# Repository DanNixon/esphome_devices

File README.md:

# ESPHome devices 

Configuration, code and CAD for custom smarthome devices, powered by [ESPHome](https://esphome.io/).

## Boards

|Board|Module|SoC|Buy|Notes|
|-----|------|---|---|-----|
|[LILYGO T-Internet POE](https://www.lilygo.cc/products/t-internet-poe)|[ESP32-WROOM-32E](https://www.espressif.com/sites/default/files/documentation/esp32-wroom-32e_esp32-wroom-32ue_datasheet_en.pdf)|[ESP32-D0WD-V3](https://www.espressif.com/sites/default/files/documentation/esp32_datasheet_en.pdf)|[AliExpress](https://www.aliexpress.com/item/4001122992446.html)||
|DOIT ESP32 DevKit USB-C|[ESP32-WROOM-32](https://www.espressif.com/sites/default/files/documentation/esp32-wroom-32_datasheet_en.pdf)|[ESP32-D0WDQ6](https://www.espressif.com/sites/default/files/documentation/esp32_datasheet_en.pdf)|[AliExpress](https://www.aliexpress.com/item/1005005495948290.html)||
|WeMos D1 Mini|TODO|[ESP8266](https://www.espressif.com/sites/default/files/documentation/esp8266-technical_reference_en.pdf)|TODO||

## Peripherals

|Type|Part|ESPHome|Buy|Notes|
|----|----|-------|---|-----|
|Temperature sensor|DS18B20|[`dallas`](https://esphome.io/components/sensor/dallas)|[AliExpress](https://www.aliexpress.com/item/1783091649.html)||
|VOC and NOx sensor|SGP41|[`sgp4x`](https://esphome.io/components/sensor/sgp4x)|[AliExpress](https://www.aliexpress.com/item/4000037083952.html)||
|CO2 sensor|SenseAir S8|[`senseair`](https://esphome.io/components/sensor/senseair)|[AliExpress](https://www.aliexpress.com/item/1005004123170360.html)|[datasheet](https://rmtplusstoragesenseair.blob.core.windows.net/docs/publicerat/PSP107.pdf)|
|Particulate matter sensor|PMS5003|[`pmsx003`](https://esphome.io/components/sensor/pmsx003)|[AliExpress](https://www.aliexpress.com/item/32944660534.html)||
|Temperature and humidity sensor|AHT20|[`aht10`](https://esphome.io/components/sensor/aht10)|[AliExpress](https://www.aliexpress.com/item/4000052449080.html)||
|Light sensor|BH1750|[`bh1750`](https://esphome.io/components/sensor/bh1750)|[AliExpress](https://www.aliexpress.com/item/1005001621873442.html)||
|IO expander|SX1509|[`sx1509`](https://esphome.io/components/sx1509)|[AliExpress](https://www.aliexpress.com/item/1005003891847975.html)||

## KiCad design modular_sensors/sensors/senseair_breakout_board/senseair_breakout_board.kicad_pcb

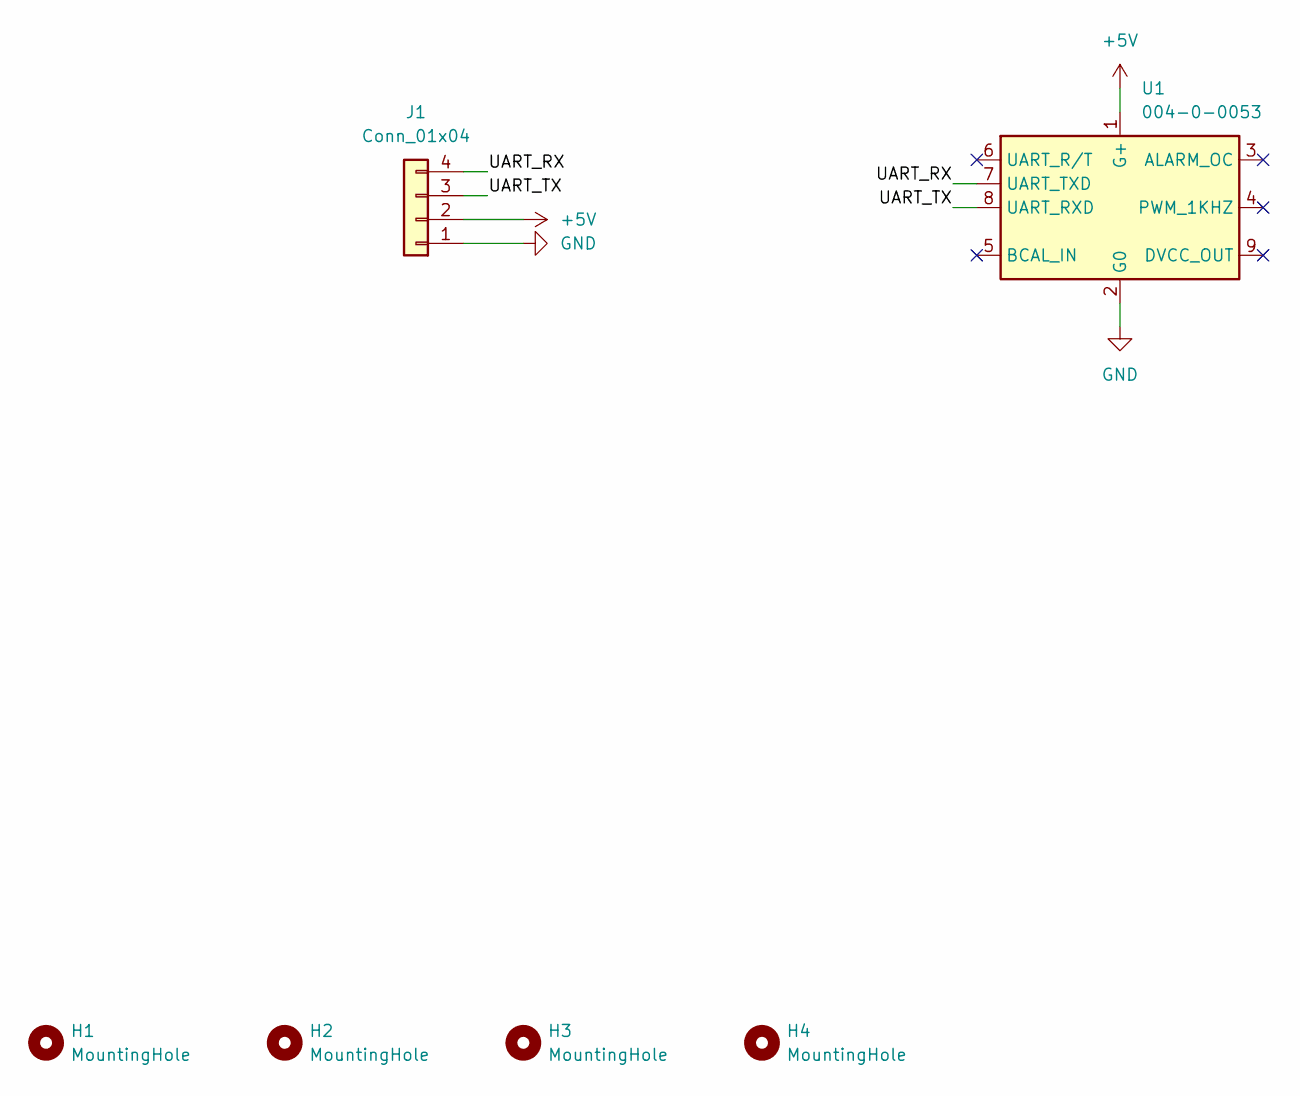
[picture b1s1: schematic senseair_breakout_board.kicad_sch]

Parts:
H1, H2, H3, H4: MountingHole; MountingHole_3.2mm_M3
J1: Conn_01x04; PinHeader_1x04_P2.54mm_Horizontal
U1: 004-0-0053; Senseair_S8_Down

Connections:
+5V: J1.2, U1.1 (G+)
/UART_RX: J1.4, U1.7 (UART_TXD)
/UART_TX: J1.3, U1.8 (UART_RXD)
GND: J1.1, U1.2 (G0)

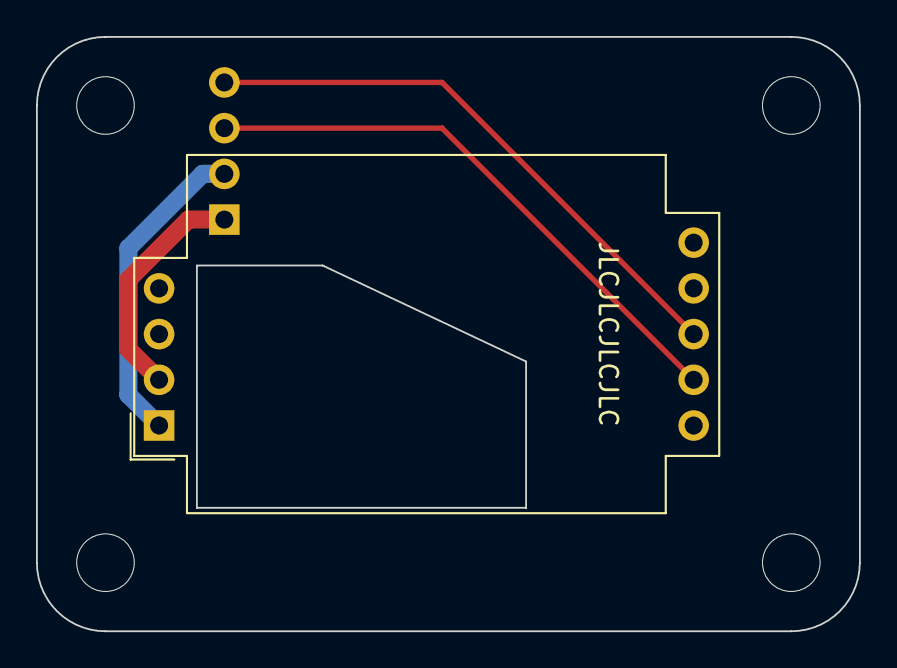
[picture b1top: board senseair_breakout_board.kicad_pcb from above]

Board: 2 copper layers, 45.7 x 33.0 mm, 6 parts (1 on the bottom side), 4 nets.

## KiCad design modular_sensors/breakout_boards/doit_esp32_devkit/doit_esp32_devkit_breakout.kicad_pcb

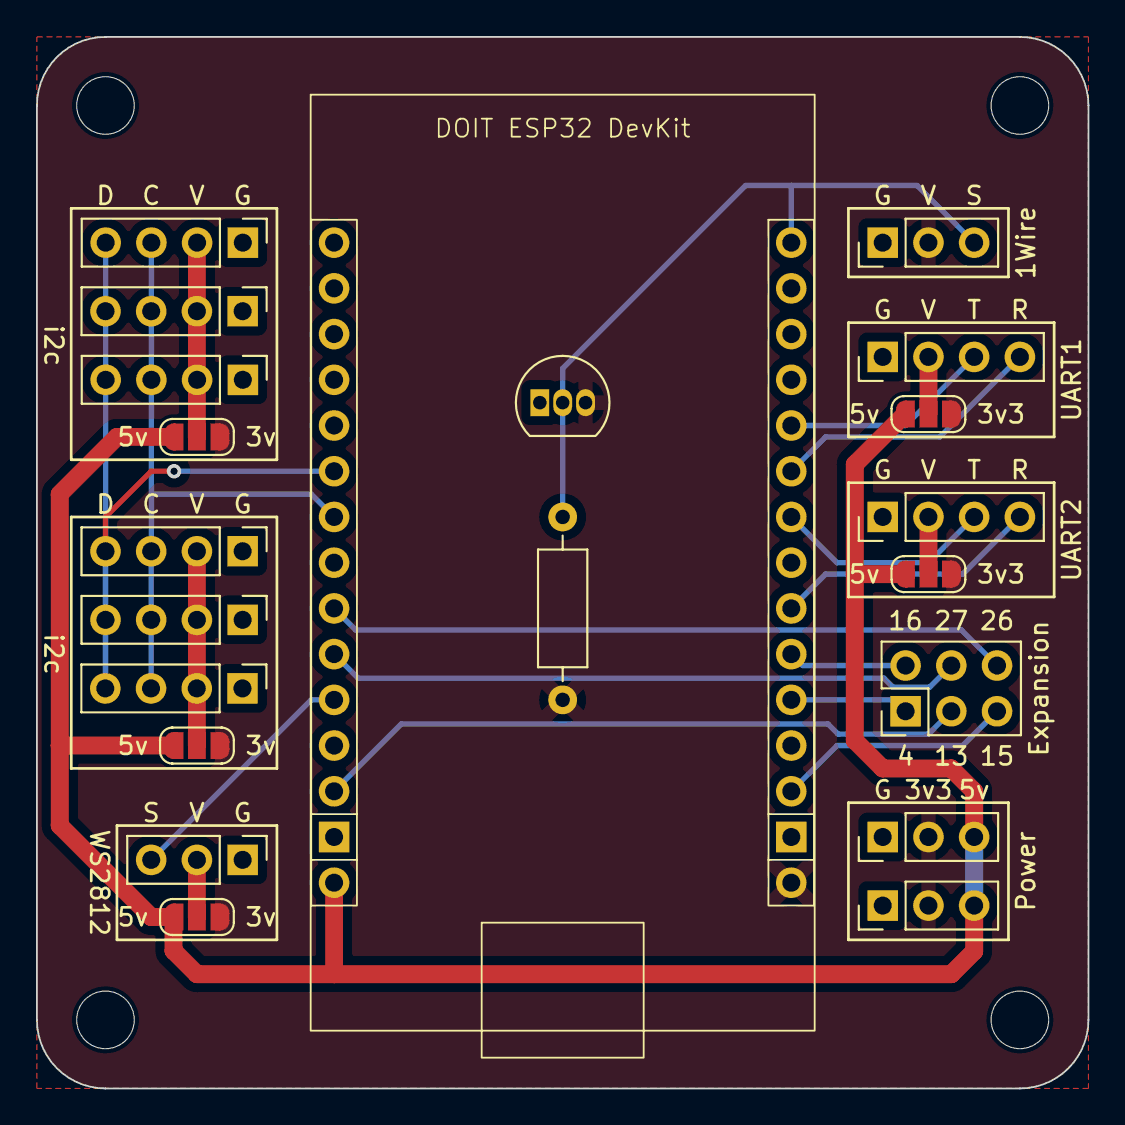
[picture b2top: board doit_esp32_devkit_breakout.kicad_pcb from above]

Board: 2 copper layers, 58.4 x 58.4 mm, 25 parts (0 on the bottom side), 22 nets.

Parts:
H1, H2, H3, H4: MountingHole; MountingHole_3.2mm_M3
J1: UART1; PinHeader_1x04_P2.54mm_Vertical
J2, J3: Power; PinHeader_1x03_P2.54mm_Vertical
J4: UART2; PinHeader_1x04_P2.54mm_Vertical
J5: Expansion; PinHeader_2x03_P2.54mm_Vertical
J6: WS2812; PinHeader_1x03_P2.54mm_Vertical
J7: OneWire; PinHeader_1x03_P2.54mm_Vertical
J8, J9, J10, J11, J12, J13: i2c; PinHeader_1x04_P2.54mm_Vertical
JP1: WS2812 V; SolderJumper-3_P1.3mm_Open_RoundedPad1.0x1.5mm_NumberLabels
JP2: UART1 V; SolderJumper-3_P1.3mm_Open_RoundedPad1.0x1.5mm_NumberLabels
JP3: UART2 V; SolderJumper-3_P1.3mm_Open_RoundedPad1.0x1.5mm_NumberLabels
JP5, JP6: i2c V; SolderJumper-3_P1.3mm_Open_RoundedPad1.0x1.5mm_NumberLabels
R1: 4K7; R_Axial_DIN0207_L6.3mm_D2.5mm_P10.16mm_Horizontal
U1: DOIT-ESP32-DEVKIT
U2: DS18B20; TO-92_Inline

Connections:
+3.3V: J2.2, J3.2, J7.2, JP1.3 (B), JP2.3 (B), JP3.3 (B), JP5.3 (B), JP6.3 (B), R1.1, U1.30 (3V3), U2.3 (V_{DD})
+5V: J2.3, J3.3, JP1.1 (A), JP2.1 (A), JP3.1 (A), JP5.1 (A), JP6.1 (A), U1.15 (VIN)
/D4: J5.1, U1.26 (D4)
/D13: J5.3, U1.13 (D13)
/D15: J5.5, U1.28 (D15)
/D16: J5.2, U1.25 (D16)
/D26: J5.6, U1.9 (D26)
/D27: J5.4, U1.10 (D27)
/I2C_SCL: J8.3, J9.3, J10.3, J11.3, J12.3, J13.3, U1.7 (D33)
/I2C_SDA: J8.4, J9.4, J10.4, J11.4, J12.4, J13.4, U1.6 (D32)
/ONEWIRE: J7.3, R1.2, U1.16 (D23), U2.2 (DQ)
/UART1_RX: J1.4, U1.21 (D19)
/UART1_TX: J1.3, U1.20 (D21)
/UART2_RX: J4.4, U1.24 (D17)
/UART2_TX: J4.3, U1.22 (D18)
/WS2812: J6.3, U1.11 (D14)
GND: J1.1, J2.1, J3.1, J4.1, J6.1, J7.1, J8.1, J9.1, J10.1, J11.1, J12.1, J13.1, U1.14 (GND), U1.29 (GND), U2.1 (GND)
unnamed: J1.2, JP2.2 (C)
unnamed: J4.2, JP3.2 (C)
unnamed: J6.2, JP1.2 (C)
unnamed: J8.2, J10.2, J12.2, JP5.2 (C)
unnamed: J9.2, J11.2, J13.2, JP6.2 (C)

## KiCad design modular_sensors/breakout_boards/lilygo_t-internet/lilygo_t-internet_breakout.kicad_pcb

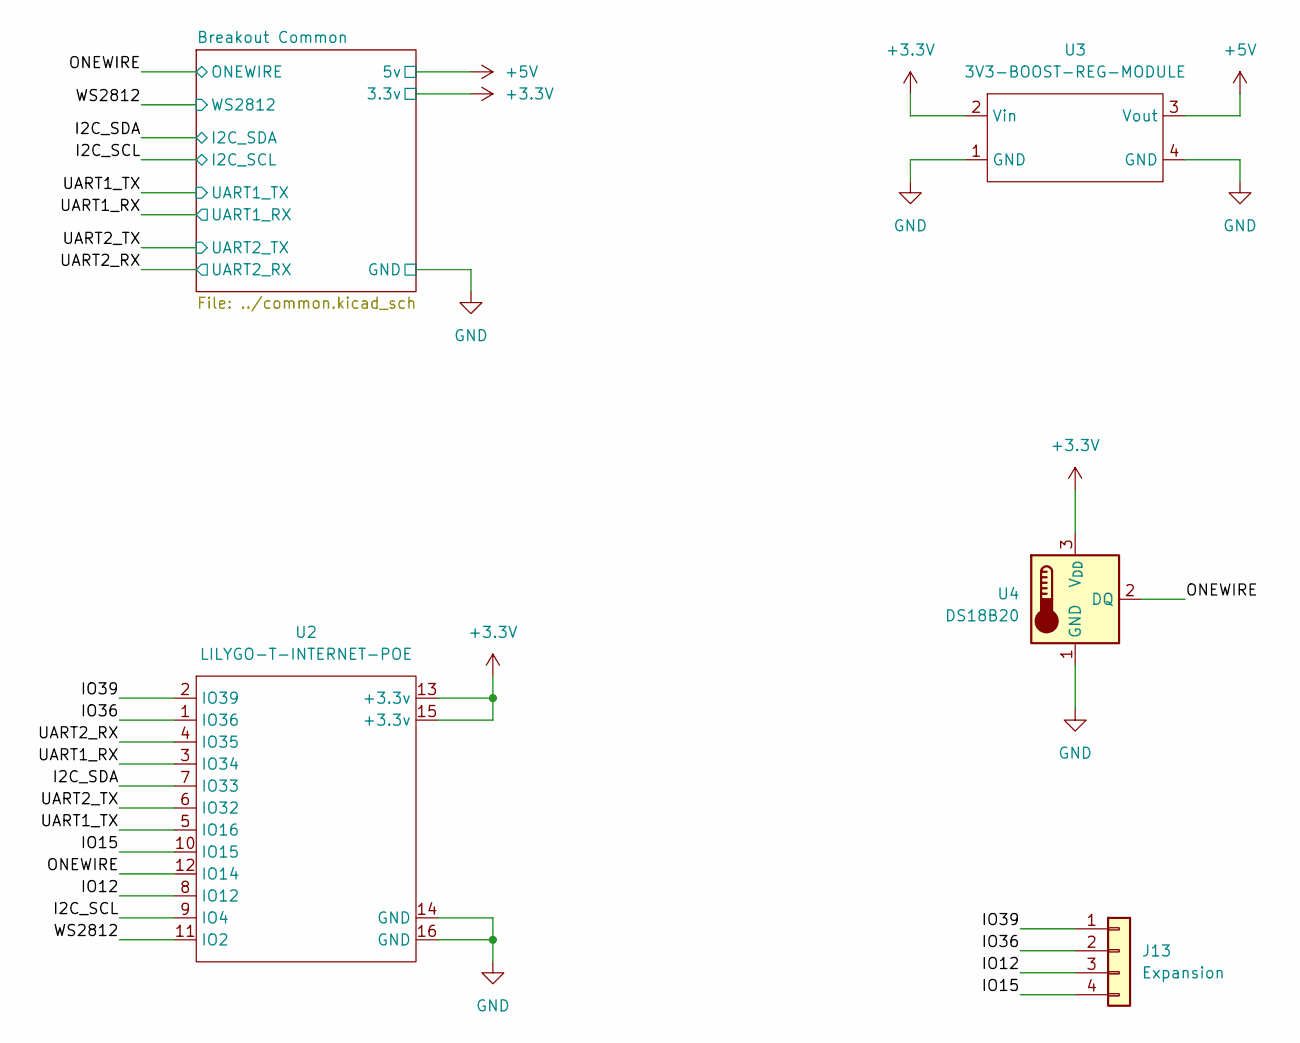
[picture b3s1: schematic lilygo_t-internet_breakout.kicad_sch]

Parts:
J13: Expansion; PinHeader_1x04_P2.54mm_Vertical
U2: LILYGO-T-INTERNET-POE
U3: 3V3-BOOST-REG-MODULE
U4: DS18B20; TO-92_Inline

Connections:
+3.3V: U2.13 (+3.3v), U2.15 (+3.3v), U3.2 (Vin), U4.3 (V_{DD}); also elsewhere on the board
+5V: U3.3 (Vout); also elsewhere on the board
/I2C_SCL: U2.9 (IO4); also elsewhere on the board
/I2C_SDA: U2.7 (IO33); also elsewhere on the board
/IO12: J13.3, U2.8 (IO12)
/IO15: J13.4, U2.10 (IO15)
/IO36: J13.2, U2.1 (IO36)
/IO39: J13.1, U2.2 (IO39)
/ONEWIRE: U2.12 (IO14), U4.2 (DQ); also elsewhere on the board
/UART1_RX: U2.3 (IO34); also elsewhere on the board
/UART1_TX: U2.5 (IO16); also elsewhere on the board
/UART2_RX: U2.4 (IO35); also elsewhere on the board
/UART2_TX: U2.6 (IO32); also elsewhere on the board
/WS2812: U2.11 (IO2); also elsewhere on the board
GND: U2.14 (GND), U2.16 (GND), U3.1 (GND), U3.4 (GND), U4.1 (GND); also elsewhere on the board

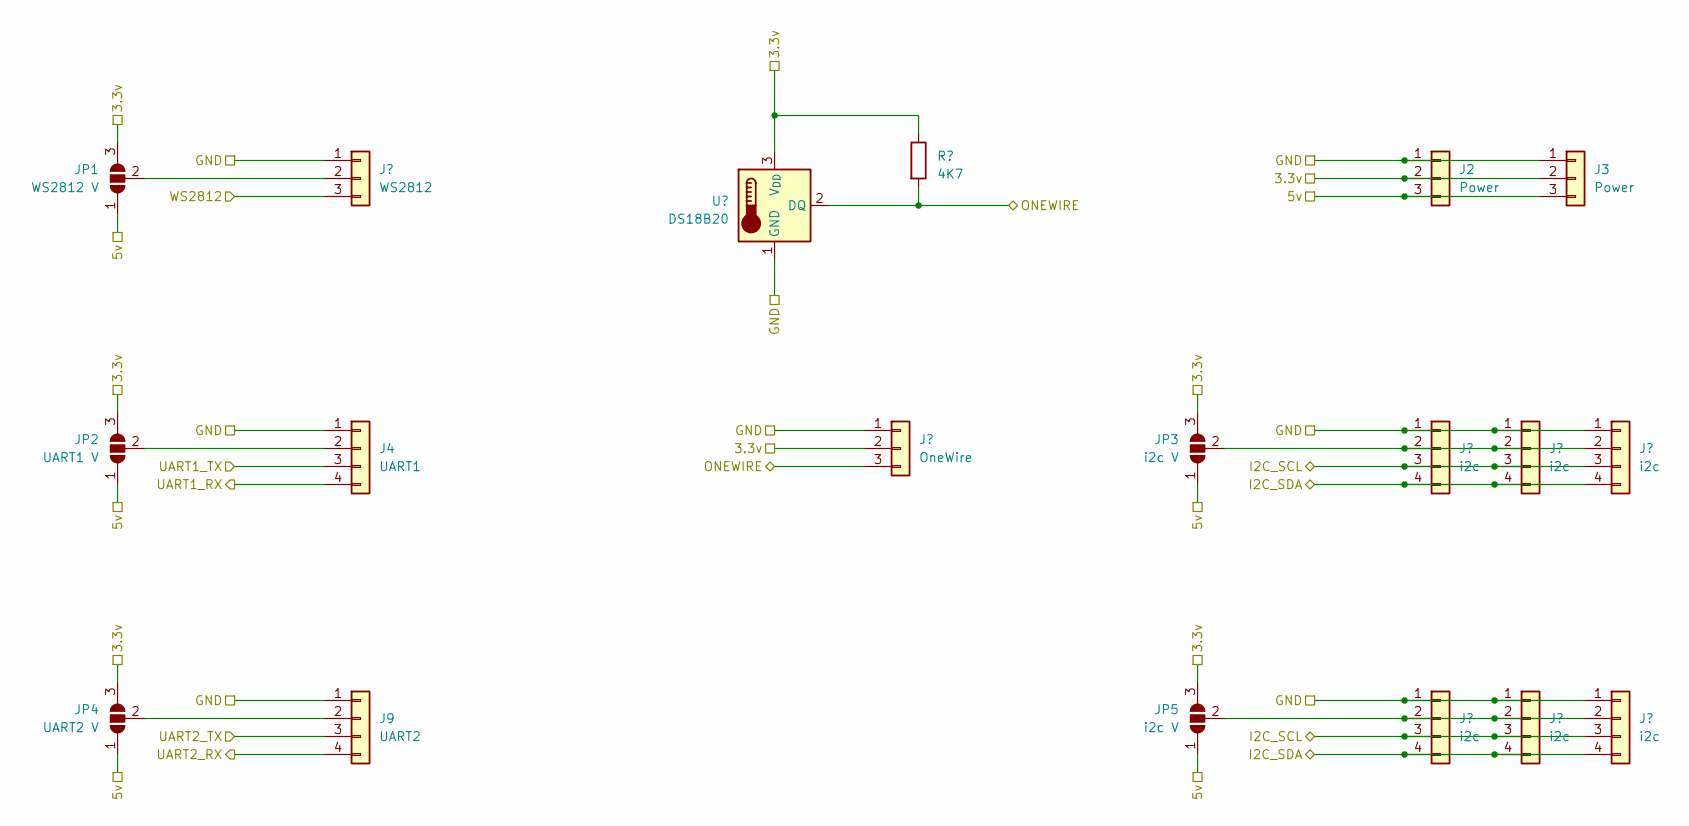
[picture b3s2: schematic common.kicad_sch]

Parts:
J1: WS2812; PinHeader_1x03_P2.54mm_Vertical
J2, J3: Power; PinHeader_1x03_P2.54mm_Vertical
J4: UART1; PinHeader_1x04_P2.54mm_Vertical
J5: OneWire; PinHeader_1x03_P2.54mm_Vertical
J6, J7, J8, J10, J11, J12: i2c; PinHeader_1x04_P2.54mm_Vertical
J9: UART2; PinHeader_1x04_P2.54mm_Vertical
JP1: WS2812 V; SolderJumper-3_P1.3mm_Open_RoundedPad1.0x1.5mm_NumberLabels
JP2: UART1 V; SolderJumper-3_P1.3mm_Open_RoundedPad1.0x1.5mm_NumberLabels
JP3, JP5: i2c V; SolderJumper-3_P1.3mm_Open_RoundedPad1.0x1.5mm_NumberLabels
JP4: UART2 V; SolderJumper-3_P1.3mm_Open_RoundedPad1.0x1.5mm_NumberLabels
R1: 4K7; R_Axial_DIN0207_L6.3mm_D2.5mm_P10.16mm_Horizontal
U1: DS18B20; TO-92_Inline

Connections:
+3.3V: J2.2, J3.2, J5.2, JP1.3 (B), JP2.3 (B), JP3.3 (B), JP4.3 (B), JP5.3 (B), R1.1, U1.3 (V_{DD}); also elsewhere on the board
+5V: J2.3, J3.3, JP1.1 (A), JP2.1 (A), JP3.1 (A), JP4.1 (A), JP5.1 (A); also elsewhere on the board
/I2C_SCL: J6.3, J7.3, J8.3, J10.3, J11.3, J12.3; also elsewhere on the board
/I2C_SDA: J6.4, J7.4, J8.4, J10.4, J11.4, J12.4; also elsewhere on the board
/ONEWIRE: J5.3, R1.2, U1.2 (DQ); also elsewhere on the board
/UART1_RX: J4.4; also elsewhere on the board
/UART1_TX: J4.3; also elsewhere on the board
/UART2_RX: J9.4; also elsewhere on the board
/UART2_TX: J9.3; also elsewhere on the board
/WS2812: J1.3; also elsewhere on the board
GND: J1.1, J2.1, J3.1, J4.1, J5.1, J6.1, J7.1, J8.1, J9.1, J10.1, J11.1, J12.1, U1.1 (GND); also elsewhere on the board
unnamed: J1.2, JP1.2 (C)
unnamed: J4.2, JP2.2 (C)
unnamed: J6.2, J7.2, J8.2, JP3.2 (C)
unnamed: J9.2, JP4.2 (C)
unnamed: J10.2, J11.2, J12.2, JP5.2 (C)

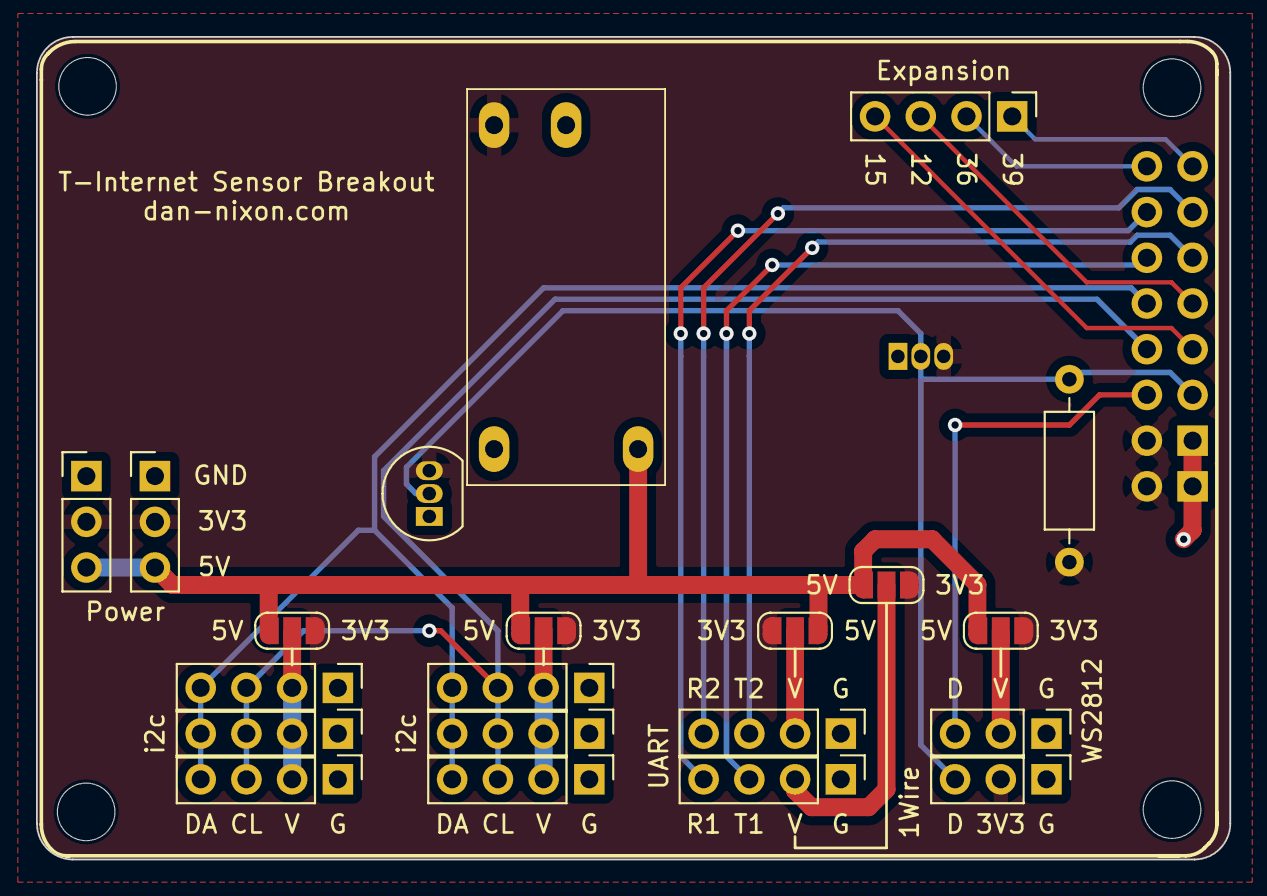
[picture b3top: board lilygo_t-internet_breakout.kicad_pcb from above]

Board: 2 copper layers, 66.3 x 45.7 mm, 23 parts (1 on the bottom side), 20 nets.

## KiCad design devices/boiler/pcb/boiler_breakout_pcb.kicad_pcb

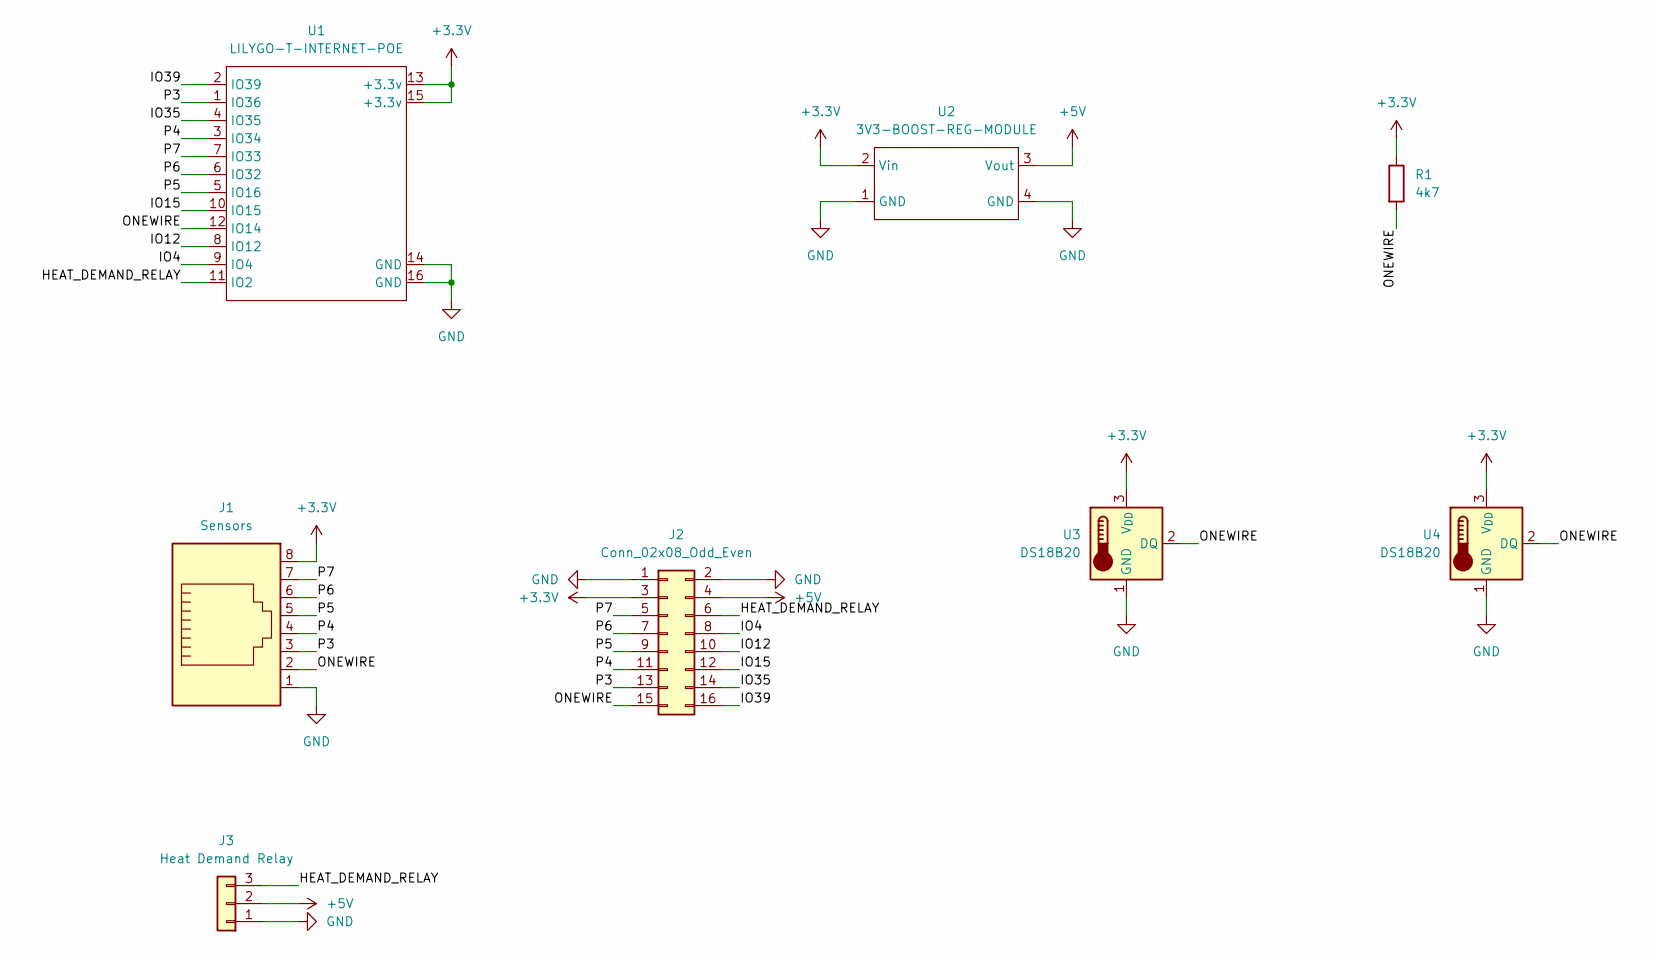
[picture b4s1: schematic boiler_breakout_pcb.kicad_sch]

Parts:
J1: Sensors; RJ45_Amphenol_54602-x08_Horizontal
J2: Conn_02x08_Odd_Even; PinHeader_2x08_P2.54mm_Vertical
J3: Heat Demand Relay; PinHeader_1x03_P2.54mm_Horizontal
R1: 4k7; R_Axial_DIN0309_L9.0mm_D3.2mm_P12.70mm_Horizontal
U1: LILYGO-T-INTERNET-POE
U2: 3V3-BOOST-REG-MODULE
U3, U4: DS18B20; TO-92_Inline

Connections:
+3.3V: J1.8, J2.3, R1.1, U1.13 (+3.3v), U1.15 (+3.3v), U2.2 (Vin), U3.3 (V_{DD}), U4.3 (V_{DD})
+5V: J2.4, J3.2, U2.3 (Vout)
/HEAT_DEMAND_RELAY: J2.6, J3.3, U1.11 (IO2)
/IO4: J2.8, U1.9 (IO4)
/IO12: J2.10, U1.8 (IO12)
/IO15: J2.12, U1.10 (IO15)
/IO35: J2.14, U1.4 (IO35)
/IO39: J2.16, U1.2 (IO39)
/ONEWIRE: J1.2, J2.15, R1.2, U1.12 (IO14), U3.2 (DQ), U4.2 (DQ)
/P3: J1.3, J2.13, U1.1 (IO36)
/P4: J1.4, J2.11, U1.3 (IO34)
/P5: J1.5, J2.9, U1.5 (IO16)
/P6: J1.6, J2.7, U1.6 (IO32)
/P7: J1.7, J2.5, U1.7 (IO33)
GND: J1.1, J2.1, J2.2, J3.1, U1.14 (GND), U1.16 (GND), U2.1 (GND), U2.4 (GND), U3.1 (GND), U4.1 (GND)

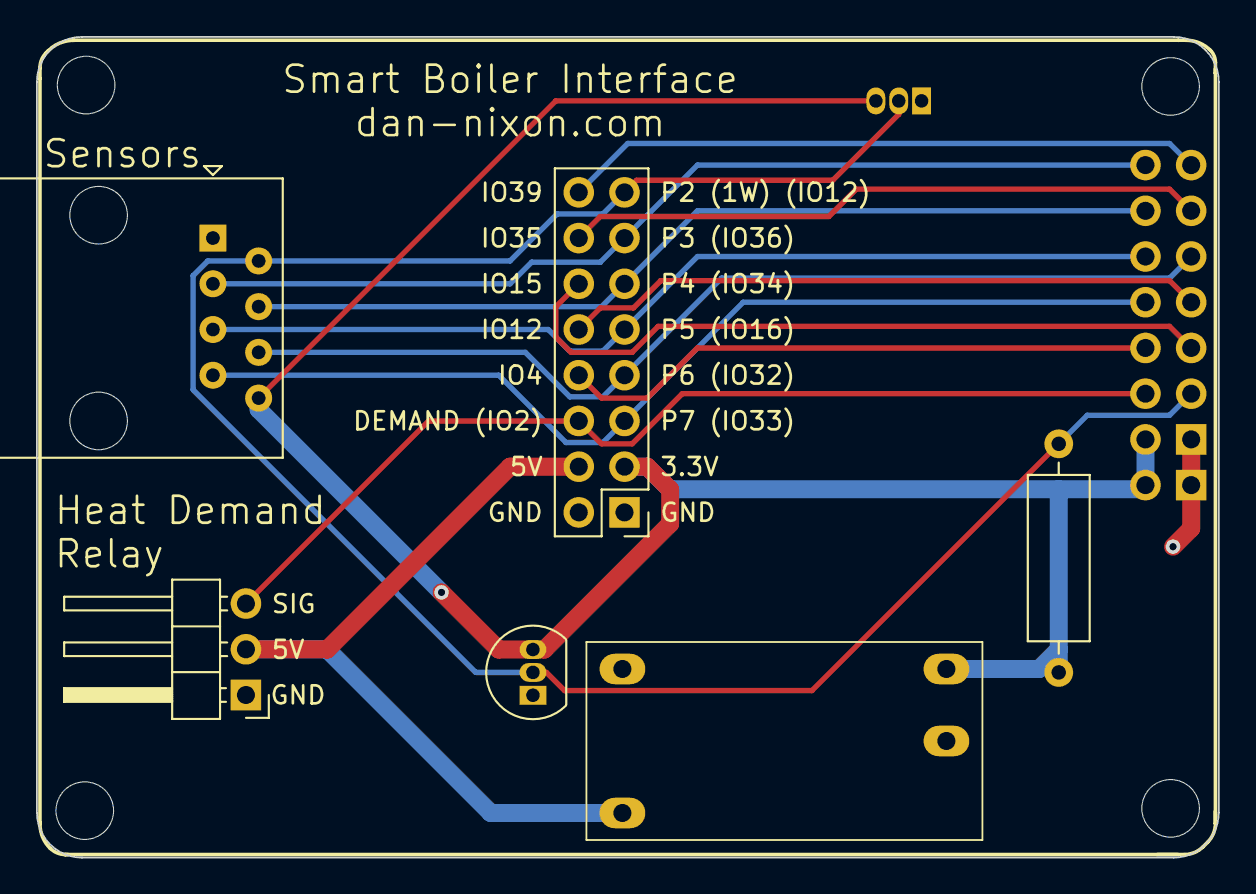
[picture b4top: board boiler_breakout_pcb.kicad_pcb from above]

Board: 2 copper layers, 65.7 x 45.6 mm, 8 parts (1 on the bottom side), 15 nets.

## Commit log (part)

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2021-08-22 Add wifi signal sensors
2021-08-27 Add heat index calculation
2023-01-18 Update CI config
2023-02-11 Remove captive portal
2023-06-20 WIP new devices
2023-06-22 Correct utility door sensor pin mapping
2023-06-25 Fix CI
2023-07-07 Front door sensor
2023-10-09 Add Nix flake
2023-10-10 Use Nix in CI
2023-10-10 Add absolute humidity calculation
2023-10-23 Add board-4
2023-10-26 Boiler interface
2023-10-26 Update CI config
    - Add missing board
    - Update action versions
    - Build on PRs
2023-10-26 Move boiler to directory
2023-10-28 Add treefmt
2023-10-28 Rename esphome common source directory
2023-10-28 CI: require quality to pass before building
2023-10-31 Move old devices
2023-11-01 Move devices to individual directories
2023-11-01 Update docs
2023-11-08 New modular sensor boards
2023-11-24 Boiler controller enclosure
2023-11-29 Second attempt at boiler enclosure
2023-12-16 Add Dependabot config
2023-12-16 Bump cachix/install-nix-action from 22 to 24
    Bumps [cachix/install-nix-action](https://github.com/cachix/install-nix-action) from 22 to 24.
    - [Release notes](https://github.com/cachix/install-nix-action/releases)
    - [Commits](https://github.com/cachix/install-nix-action/compare/v22...v24)
    ---
    updated-dependencies:
    - dependency-name: cachix/install-nix-action
2024-01-15 Bump cachix/install-nix-action from 24 to 25
    Bumps [cachix/install-nix-action](https://github.com/cachix/install-nix-action) from 24 to 25.
    - [Release notes](https://github.com/cachix/install-nix-action/releases)
    - [Commits](https://github.com/cachix/install-nix-action/compare/v24...v25)
    ---
    updated-dependencies:
    - dependency-name: cachix/install-nix-action
2024-03-11 Bump cachix/install-nix-action from 25 to 26
    Bumps [cachix/install-nix-action](https://github.com/cachix/install-nix-action) from 25 to 26.
    - [Release notes](https://github.com/cachix/install-nix-action/releases)
    - [Commits](https://github.com/cachix/install-nix-action/compare/v25...v26)
    ---
    updated-dependencies:
    - dependency-name: cachix/install-nix-action
2024-05-20 Bump cachix/install-nix-action from 26 to 27
    Bumps [cachix/install-nix-action](https://github.com/cachix/install-nix-action) from 26 to 27.
    - [Release notes](https://github.com/cachix/install-nix-action/releases)
    - [Commits](https://github.com/cachix/install-nix-action/compare/v26...V27)
    ---
    updated-dependencies:
    - dependency-name: cachix/install-nix-action
2024-09-16 Bump cachix/install-nix-action from V27 to 28
    Bumps [cachix/install-nix-action](https://github.com/cachix/install-nix-action) from V27 to 28. This release includes the previously tagged commit.
    - [Release notes](https://github.com/cachix/install-nix-action/releases)
    - [Commits](https://github.com/cachix/install-nix-action/compare/V27...V28)
    ---
    updated-dependencies:
    - dependency-name: cachix/install-nix-action
2024-09-16 Set dependabot to monthly
2024-10-01 Bump cachix/install-nix-action from V28 to 29
    Bumps [cachix/install-nix-action](https://github.com/cachix/install-nix-action) from V28 to 29. This release includes the previously tagged commit.
    - [Release notes](https://github.com/cachix/install-nix-action/releases)
    - [Commits](https://github.com/cachix/install-nix-action/compare/V28...v29)
    ---
    updated-dependencies:
    - dependency-name: cachix/install-nix-action
2024-11-01 Bump cachix/install-nix-action from 29 to 30
    Bumps [cachix/install-nix-action](https://github.com/cachix/install-nix-action) from 29 to 30.
    - [Release notes](https://github.com/cachix/install-nix-action/releases)
    - [Commits](https://github.com/cachix/install-nix-action/compare/v29...v30)
    ---
    updated-dependencies:
    - dependency-name: cachix/install-nix-action
2024-12-09 Switch to nixpkgs 24.11
2025-04-01 Bump cachix/install-nix-action from 30 to 31
    Bumps [cachix/install-nix-action](https://github.com/cachix/install-nix-action) from 30 to 31.
    - [Release notes](https://github.com/cachix/install-nix-action/releases)
    - [Commits](https://github.com/cachix/install-nix-action/compare/v30...v31)
    ---
    updated-dependencies:
    - dependency-name: cachix/install-nix-action
2025-05-14 Fix OTA config
2025-05-14 Remove old devices
2025-05-14 Use devenv to provide toolchain
2025-09-02 Bump actions/checkout from 4 to 5
    Bumps [actions/checkout](https://github.com/actions/checkout) from 4 to 5.
    - [Release notes](https://github.com/actions/checkout/releases)
    - [Changelog](https://github.com/actions/checkout/blob/main/CHANGELOG.md)
    - [Commits](https://github.com/actions/checkout/compare/v4...v5)
    ---
    updated-dependencies:
2025-11-17 Update devenv.sh inputs
2025-11-17 Update secrets script for new password manager
2025-11-17 Replace utility room climate sensor
2025-12-01 Bump actions/checkout from 5 to 6
    Bumps [actions/checkout](https://github.com/actions/checkout) from 5 to 6.
    - [Release notes](https://github.com/actions/checkout/releases)
    - [Changelog](https://github.com/actions/checkout/blob/main/CHANGELOG.md)
    - [Commits](https://github.com/actions/checkout/compare/v5...v6)
    ---
    updated-dependencies:
2026-01-20 Switch to flake
2026-04-01 Bump cachix/cachix-action from 16 to 17
    Bumps [cachix/cachix-action](https://github.com/cachix/cachix-action) from 16 to 17.
    - [Release notes](https://github.com/cachix/cachix-action/releases)
    - [Commits](https://github.com/cachix/cachix-action/compare/v16...v17)
    ---
    updated-dependencies:
    - dependency-name: cachix/cachix-action
